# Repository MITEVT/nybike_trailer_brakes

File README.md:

nybike_trailer_brakes
=====================

EVT hardware and firmware for DCMotor actuated trailer saftey brakes.

Takes input from button and gives power to a motor in the forward direction. When the button is released, the motor spins back.

Integrated H-Bridge L 298N used.

Directory Structure
---------------------
firmware - directory containing all firmware for the project

hardware - contains part specifications and board layouts

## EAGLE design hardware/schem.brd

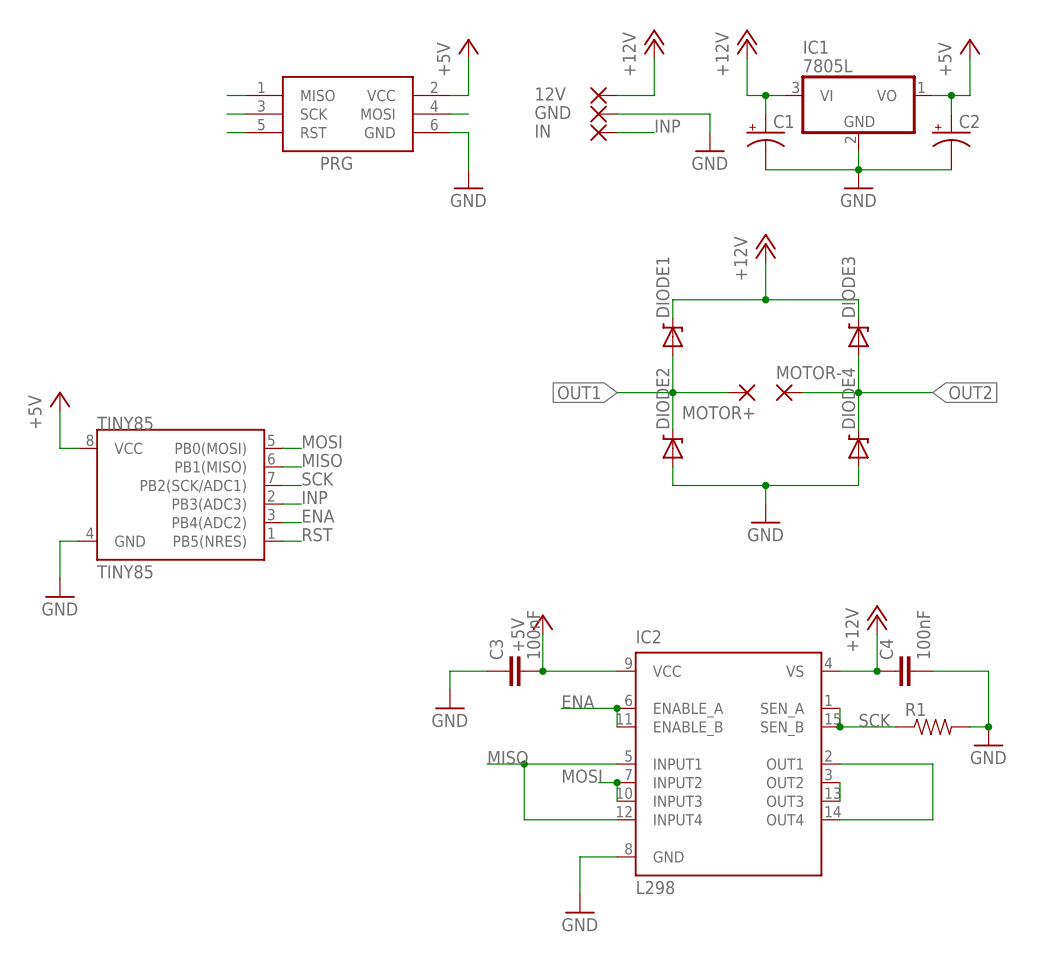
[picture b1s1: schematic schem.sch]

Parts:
12V: 3,81/1,4
C1, C2: CPOL-USE2.5-6; E2,5-6
C3, C4: 100nF; CAP-PTH-SMALL2
DIODE1, DIODE2, DIODE3, DIODE4: DIODE-ZENERPTH; DIODE-ZENER
GND: 3,81/1,4
IC1: 7805L; TO92
IC2: L298; MULTIWATT-15
IN: 1,6/0,9
MOTOR+: 3,81/1,4
MOTOR-: 3,81/1,4
PRG: AVRISP-6; AVRISP
R1: RESISTORPTH-1/4W; AXIAL-0.4
TINY85: TINY85; DIP08

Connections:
+5V: C2.+, C3.2, IC1.1 (VO), IC2.9 (VCC), PRG.2 (VCC), TINY85.8 (VCC)
+12V: 12V.1, C1.+, C4.1, DIODE1.P$1 (C), DIODE3.P$1 (C), IC1.3 (VI), IC2.4 (VS)
ENA: IC2.6 (ENABLE_A), IC2.11 (ENABLE_B), TINY85.3 (PB4(ADC2))
GND: C1.-, C2.-, C3.1, C4.2, DIODE2.P$2 (A), DIODE4.P$2 (A), GND.1, IC1.2 (GND), IC2.8 (GND), PRG.6 (GND), R1.P$2 (2), TINY85.4 (GND)
INP: IN.1, TINY85.2 (PB3(ADC3))
MISO: IC2.5 (INPUT1), IC2.12 (INPUT4), PRG.1 (MISO), TINY85.6 (PB1(MISO))
MOSI: IC2.7 (INPUT2), IC2.10 (INPUT3), PRG.4 (MOSI), TINY85.5 (PB0(MOSI))
OUT1: DIODE1.P$2 (A), DIODE2.P$1 (C), IC2.2 (OUT1), IC2.14 (OUT4), MOTOR+.1
OUT2: DIODE3.P$2 (A), DIODE4.P$1 (C), IC2.3 (OUT2), IC2.13 (OUT3), MOTOR-.1
RST: PRG.5 (RST), TINY85.1 (PB5(NRES))
SCK: IC2.1 (SEN_A), IC2.15 (SEN_B), PRG.3 (SCK), R1.P$1 (1), TINY85.7 (PB2(SCK/ADC1))

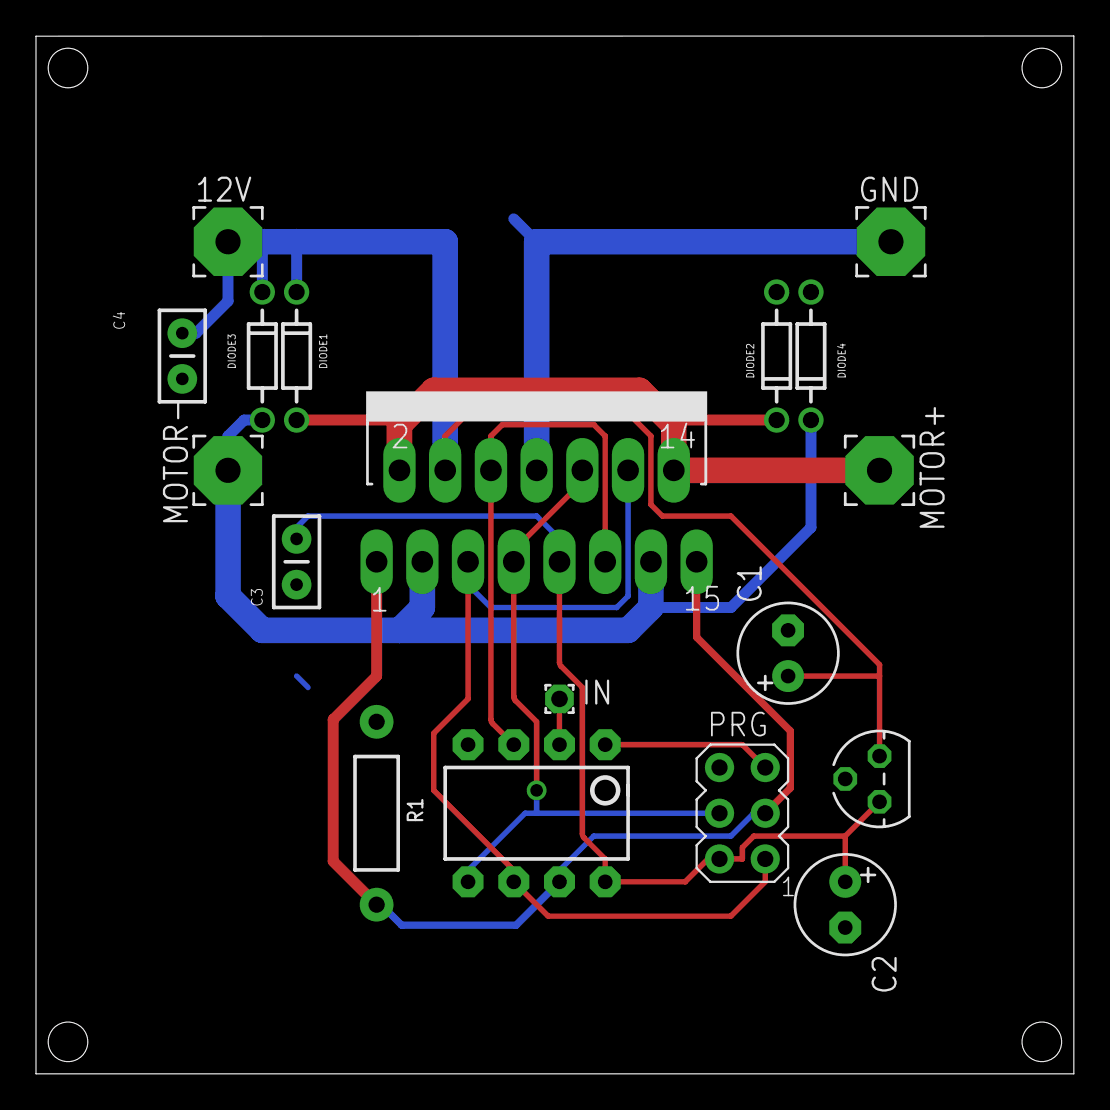
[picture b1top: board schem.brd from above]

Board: 2 copper layers, 57.7 x 57.7 mm, 18 parts (0 on the bottom side), 11 nets.

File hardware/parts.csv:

Part;Value;Device;Package;Description;MF;MPN;OC_FARNELL;OC_NEWARK;PROD_ID;VALUE;
"12V";"";"3,81/1,4";"3,81/1,4";"THROUGH-HOLE PAD";"";"";"";"";"";"";
"C1";"";"CPOL-USE2.5-6";"E2,5-6";"POLARIZED CAPACITOR, American symbol";"";"";"";"";"";"";
"C2";"";"CPOL-USE2.5-6";"E2,5-6";"POLARIZED CAPACITOR, American symbol";"";"";"";"";"";"";
"C3";"100nF";"CAPPTH2";"CAP-PTH-SMALL2";"Capacitor";"";"";"";"";"";"";
"C4";"100nF";"CAPPTH2";"CAP-PTH-SMALL2";"Capacitor";"";"";"";"";"";"";
"DIODE1";"DIODE-ZENERPTH";"DIODE-ZENERPTH";"DIODE-ZENER";"Zener Diode";"";"";"";"";"";"";
"DIODE2";"DIODE-ZENERPTH";"DIODE-ZENERPTH";"DIODE-ZENER";"Zener Diode";"";"";"";"";"";"";
"DIODE3";"DIODE-ZENERPTH";"DIODE-ZENERPTH";"DIODE-ZENER";"Zener Diode";"";"";"";"";"";"";
"DIODE4";"DIODE-ZENERPTH";"DIODE-ZENERPTH";"DIODE-ZENER";"Zener Diode";"";"";"";"";"";"";
"GND";"";"3,81/1,4";"3,81/1,4";"THROUGH-HOLE PAD";"";"";"";"";"";"";
"IC1";"7805L";"7805L";"TO92";"Positive VOLTAGE REGULATOR";"";"";"";"";"";"";
"IC2";"L298";"L298";"MULTIWATT-15";"DUAL FULL-BRIDGE DRIVER";"";"L298N";"1589425";"32M1527";"";"";
"IN";"";"1,6/0,9";"1,6/0,9";"THROUGH-HOLE PAD";"";"";"";"";"";"";
"MOTOR+";"";"3,81/1,4";"3,81/1,4";"THROUGH-HOLE PAD";"";"";"";"";"";"";
"MOTOR-";"";"3,81/1,4";"3,81/1,4";"THROUGH-HOLE PAD";"";"";"";"";"";"";
"PRG";"AVRISP-6";"AVRISP-6";"AVRISP";"AVR ISP HEADER";"";"";"";"";"";"";
"R1";"";"RESISTORPTH-1/4W";"AXIAL-0.4";"Resistor";"";"";"";"";"";"";
"TINY85";"TINY85";"ATTINY45TINY85-20-DIP";"DIP08";"Atmel 8-pin 2/4/8kB flash uC";"";"";"";"";"IC-09445";"TINY85-20-DIP";

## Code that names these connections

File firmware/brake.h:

#include <avr/io.h>
#include <avr/interrupt.h>
#include <util/delay.h>

//outputs
#define OUT1 PB1 //Pin 6
#define OUT2 PB0 //Pin 7
#define ENA  PB4 //Pin 3

//inputs
#define INPUT PB3 //Pin 2
#define ISense PB2 


#define set_up_input() (PORTB |= (1 << INPUT))
#define set_up_output() (DDRB |= (1 << OUT1) | (1 << OUT2) | (1 << ENA))

//Set single ended input on PB2, Prescale by 8 to get 125kHz Sample frequency, and enable
#define set_up_adc() {ADMUX |= (1 << MUX0) | (0 << ADLAR); ADCSRA |= (1 << ADPS1) | (1 << ADPS0); ADCSRA |= (1 << ADEN);}

#define start_adc() (ADCSRA |= (1 << ADSC))
#define adc_is_running() ((ADCSRA & (1 << ADSC)) >> ADSC)
#define get_value() (ADCL + (ADCH << 8))

#define set_up_timer0() { \
	TCCR0B |= (1 << CS01); \
	TIMSK |= (1 << TOIE0); \
}

#define set_up_timer1(pwm) { \
	OCR1B = 0; \
	OCR1C = pwm; \
	TCCR1 |= (1 << CS11) | (1 << CS10); \
	GTCCR |= (1 << PWM1B) | (1 << COM1B1); \
	PLLCSR |= (1 << PLLE); \
	_delay_us(100); \
	while(!(PLLCSR & (1 << PLOCK))) {} \
	PLLCSR |= (1 << PCKE); \
}

#define disable_interrupt() (TIMSK &= ~(1 << TOIE1))
#define reset_timer() (TCNT1 = 0)
#define enable_interrupt() (TIMSK |= (1 << TOIE1))

#define set_duty(duty) (OCR1B = duty)
#define get_input() ((PINB & (1 << INPUT)))

#define set_out1_high() (PORTB |= (1 << OUT1))
#define set_out1_low() (PORTB &= ~(1 << OUT1))
#define set_out2_high() (PORTB |= (1 << OUT2))
#define set_out2_low() (PORTB &= ~(1 << OUT2))
#define set_enable_high() (PORTB |= (1 << ENA))
#define set_enable_low() (PORTB &= ~(1 << ENA))

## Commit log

2013-10-18 added to the README
    initial local commit
2013-10-18 added directory stuff to readme
2013-10-18 updated directory structure
2013-10-18 Added firmware files
2013-10-18 Added Hardware and updated .gitignore
2013-10-18 added .gitignore
2013-10-18 added MIT liscense
2013-10-18 .DS_Store banished
2013-10-18 Added extra details to project summary
2013-11-04 Updated Schematic and Board with new design
    Changed style of board to H-Bridge for DCMotor
2013-11-04 Updated Schematic to use integrated H Bridge with DC Motor
2013-11-04 Updated Board and Schematic
    Preliminary routing accomplished
2013-11-04 Added Integrated H-Bridge name
2013-11-04 Updated Schematic and Board to include AVR ISP Header
    Changed the structure of the H Bridge as well. No longer are you able to independently control all 4 "switches". Now, you control the motor with tow pins (forward or reverse). Layout has yet to bo op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
2013-11-04 Updated README'
2013-11-04 Added ISP Header to board and schematic
2013-11-04 Cleaned up Schematic and Hand Routed Board
2013-11-04 Saved project file
2013-11-05 Cleaned up Schematic and fixed transitors
2013-11-05 added connections from tiny to HBridge
2013-11-05 Routed board
2013-11-05 changed pin inputs and re-rounted
2013-11-05 compated board size
2013-11-08 selencetd new mosfets and routed
2013-11-08 added large ground plane and power supply capacitors
2013-11-08 Removed power transistor from ground plane
2013-11-08 modified silkscreen and worked on Power supply capacitor placement
2013-11-09 Updated Schematic
    Used new IC H Bridge and cleaned up schematic
2013-11-09 Updated silk screen and moved components on board
2013-11-09 Cleaned up board and moved around components
    Made space to give H Bridge room to breath
    Imporved Silk Screen
2013-11-09 Improved ground plane
2013-11-09 cleaned up ground pour and outline
2013-11-11 switched enable to a pin with PWM output
2013-11-11 added current sensing
2013-11-13 first software commit
2013-11-13 added IO access methods
2013-11-16 more structs for state
2013-11-16 Implemented getNewState function
2013-11-16 Added cycle functionality to getNextState()
2013-11-16 Changed Current Sense pin
2013-11-16 added ADC init
2013-11-16 Implemented Current Sensing
2013-11-18 Restructured Program
    getNextState no longer sets the action to be done, doAction handles that
2013-11-20 Added BoM
2013-11-20 Removed old parts list
2013-11-20 Implemented stopBrake()
2013-11-20 Added interrupt functionality
    Next state is set on timer 1 overflow and proper action is started
2013-11-21 Improved and added comments
2013-11-23 Replaced diodes
2013-11-23 Added opening time functionality
2013-12-07 added mounting holes
2013-12-09 ground plane and silk screen in prep for fab
2013-12-13 Changed to driver structure
2014-01-08 Fixed timer code
2014-01-15 Fixed a bunch of bugs
2014-01-17 Switched over to Timer 0 for interrupts
    Timer 1 now only supplies a stable PWM signal for the enable pin. Timer 0 provides the interrupts for logic functionality. Prevents future code from harming enable pwm integrity.
2014-01-17 Removed accidental changes meant for TwoTimers
2014-01-17 Latest changes
2014-01-17 Implemented two timer method and fixed several bugs. Working sans ADC
2014-01-17 wow I'm a mornon
2014-01-17 Recovered from the disastrous merge
2014-01-17 ADC current sensing implemented and working
2014-01-18 Updated git ignore
2014-01-18 Removed hex files
2014-01-23 Fixed forward stop and added reverse tap
2014-06-20 Added instructions to increase strength

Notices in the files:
parts and their libraries:
SparkFun-DigitalIC: Licensing: CC v3.0 Share-Alike You are welcome to use this library for commercial purposes.
